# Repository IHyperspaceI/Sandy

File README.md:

ATTiny works but needs redesign as ground pours are not connected. Hence, the IMU does not get power. The focus on small packaging led to certain compromises in layout, ultimately bringing the project's downfall.
Unfortunately, KiCAD was not configured to highlight isolated GNDs, and this oversight led to the issues.

Top Layer:

Bottom Layer

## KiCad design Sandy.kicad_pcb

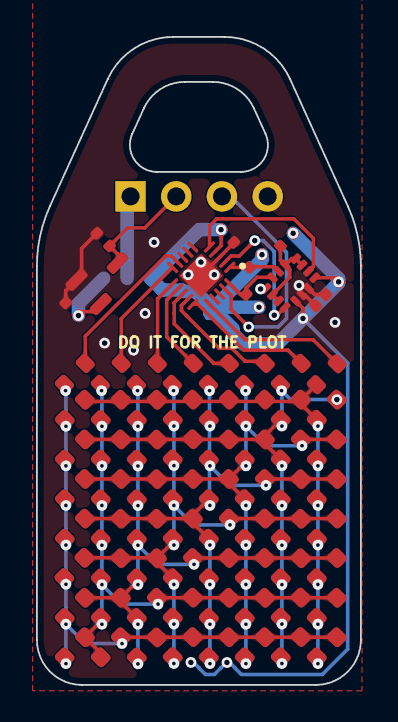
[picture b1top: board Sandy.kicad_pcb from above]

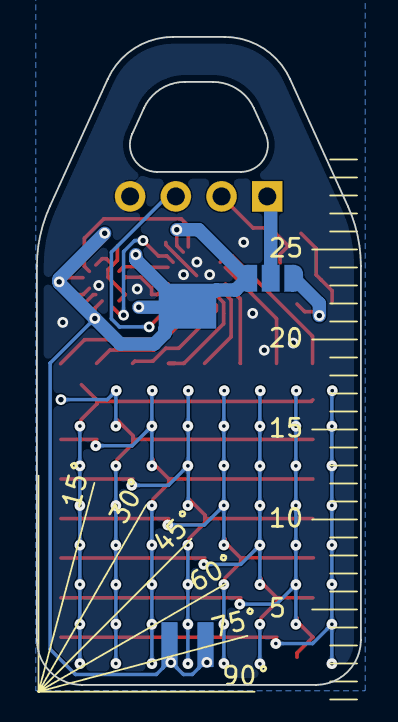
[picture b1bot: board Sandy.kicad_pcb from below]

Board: 2 copper layers, 18.0 x 36.0 mm, 78 parts (2 on the bottom side), 19 nets.

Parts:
BT1: Battery_Cell; BatteryHolder_Keystone_3092_Fucked_1.6x16mm
C1, C3, C4: 100nF; C_0402
C2, C5: 1uF; C_0402
D1, D2, D3, D4, D5, D6, D7, D8, D9, D10, D11, D12, D13, D14, D15, D16, D17, D18, D19, D20, D21, D22, D23, D24, D25, D26, D27, D28, D29, D30, D31, D32, D33, D34, D35, D36, D37, D38, D39, D40, D41, D42, D43, D44, D45, D46, D47, D48, D49, D50, D51, D52, D53, D54, D55, D56: Green; D_0603
J1: Conn_01x04_Socket; PinHeader_1x04_P2.54mm_Vertical
JP1: SolderJumper_3_Open; SolderJumper-3_P1.3mm_Open_RoundedPad1.0x1.5mm
R1, R2: 4.7kΩ; R_0402
R3, R4, R5, R6, R7, R8, R9, R10: 22Ω; R_0603
R11: 10kΩ; R_0402
U1: ATtiny1616-M; VQFN-20-1EP_3x3mm_P0.4mm_EP1.7x1.7mm
U2: XC6206P332MR-G; SOT-23-3
U3: LSM6DSVE; LGA-14_3x2.5mm_P0.5mm_LayoutBorder3x4y

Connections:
3V3: BT1.1 (+_1), C1.1, C3.1, C4.1, JP1.1 (A), R1.1, R2.1, R11.1, U1.4 (VCC), U3.5 (VDDIO), U3.8 (VDD)
3V3_PORT: J1.1, JP1.2 (C)
3V3_REG: C5.1, JP1.3 (B), U2.2 (VO)
/INT1: U1.2 (PA3), U3.4 (INT1)
/INT2: U1.5 (PA4), U3.9 (INT2)
/PORT0: D1.2, D2.2, D3.2, D4.2, D5.2, D6.2, D7.2, D14.1, D21.1, D28.1, D35.1, D42.1, D49.1, D56.1, R10.1, R10.2, U1.9 (PB5)
/PORT1: D7.1, D8.2, D9.2, D10.2, D11.2, D12.2, D13.2, D14.2, D20.1, D27.1, D34.1, D41.1, D48.1, D55.1, R9.1, R9.2, U1.10 (PB4)
/PORT2: D6.1, D13.1, D15.2, D16.2, D17.2, D18.2, D19.2, D20.2, D21.2, D26.1, D33.1, D40.1, D47.1, D54.1, R8.1, R8.2, U1.11 (PB3)
/PORT3: D5.1, D12.1, D19.1, D22.2, D23.2, D24.2, D25.2, D26.2, D27.2, D28.2, D32.1, D39.1, D46.1, D53.1, R7.1, R7.2, U1.12 (PB2)
/PORT4: D4.1, D11.1, D18.1, D25.1, D29.2, D30.2, D31.2, D32.2, D33.2, D34.2, D35.2, D38.1, D45.1, D52.1, R6.1, R6.2, U1.13 (PB1)
/PORT5: D3.1, D10.1, D17.1, D24.1, D31.1, D36.2, D37.2, D38.2, D39.2, D40.2, D41.2, D42.2, D44.1, D51.1, R5.1, R5.2, U1.14 (PB0)
/PORT6: D2.1, D9.1, D16.1, D23.1, D30.1, D37.1, D43.2, D44.2, D45.2, D46.2, D47.2, D48.2, D49.2, D50.1, R4.1, R4.2, U1.15 (PC0)
/PORT7: D1.1, D8.1, D15.1, D22.1, D29.1, D36.1, D43.1, D50.2, D51.2, D52.2, D53.2, D54.2, D55.2, D56.2, R3.1, R3.2, U1.16 (PC1)
/SCL: R2.2, U1.1 (PA2), U3.13 (SCL)
/SDA: R1.2, U1.20 (PA1), U3.14 (SDA)
/UPDI: J1.3, U1.19 (~RESET/PA0)
GND: C1.2, C2.2, C3.2, C4.2, C5.2, J1.4, U1.3 (GND), U1.21 (GND), U2.1 (GND), U3.1 (SDO/SA0), U3.6 (GND), U3.7 (GND)
unnamed: R11.2, U3.2 (SDX), U3.3 (SCX), U3.10 (OCS_Aux), U3.11 (SDO_Aux), U3.12 (CS)
VBAT+: C2.1, J1.2, U2.3 (VI)

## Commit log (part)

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2026-05-14 Release
